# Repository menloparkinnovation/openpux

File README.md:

Openpux Internet Of Things (IOT) Framework
==========================================

Copyright (C) 2018 Menlo Park Innovation LLC

   menloparkinnovation.com
   menloparkinnovation@gmail.com

> Last update 03/07/2018

# Openpux Sub Projects

## openpux:

  Node.js based IoT server with in memory or Amazon SimpleDB data stores.

  > Development is frozen, as a serverless version openpux4 is in development.
  > Still useful as a local server for RaspberryPi, or small cloud IaaS VM's
    such as AWS LightSail.

## nodejs/dweet:

  Node.js utility providing both a command line embedded device configuration
          utility and IoT gateway on RaspberryPi, Mac, PC, or Linux.

## Arduino/Libraries:

  MenloFramework, a framework approach to creating embedded firmware for Arduino
  supporting AtMega328, AVR/Mega, and ARM32/SAM/Due. This has been validated
  against Arduino IDE 1.6.4 and test/regression scripts are in tests/mac.

  > The framework architecture also supports ports to RFDuino (ARM/BLE),
  > SparkCore, (Photon/Particle), and variants such as Galileo/Edison (x86/Linux).

  > Tested versions of these ports will be in future updates as re-validation
  > against the latest releases from these providers is in progress.

## Arduino/<project_name>:

  IoT projects using the MenloFramework and communicating with the openpux
  IoT server.

## Hardware:

  MenloPark Innovation LLC hardware projects for IoT scenarios.

  All projects use the Eagle design software, and generally fit within
  the free versions limits.

  Designs have been tested by generating boards from OshPark.

## FPGA Hardware:

  menlo_cnc - FPGA based CNC controller with embedded Linux.

  fpga/de10_nano_shell - Silicon Shell for Terasic DE110-Nano-SoC board.

  menlo_gigatron - FPGA implementation of the Gigatron (gigatron.io)

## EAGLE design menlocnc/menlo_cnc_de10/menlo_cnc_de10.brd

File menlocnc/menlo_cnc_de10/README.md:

MenloCNC Breakout board for Terasic DE10-Standard
=======================================================

Copyright (C) 2018 Menlo Park Innovation LLC

   menloparkinnovation.com
   menloparkinnovation@gmail.com

> Last update 06/11/2018

# Breakout board for Menlo CNC on DE10-Standard

  > Provides Arduino UNO pin outs for GRBL Shields

  > Provides Arduino MEGA pin outs for Mendel Shields

  > Provides general purpose I/O to FPGA pins

# Uses free version of Eagle Software

  > Most popular small board design software for open source projects

  > Used by Arduino, many others

# Boards Produced by OshPark

  > Popular service for low cost boards in about 2 weeks

  > 3 boards about $39

  > Can be produced by others from standard Eagle files

  > Or use Eagle to generate Gerber files

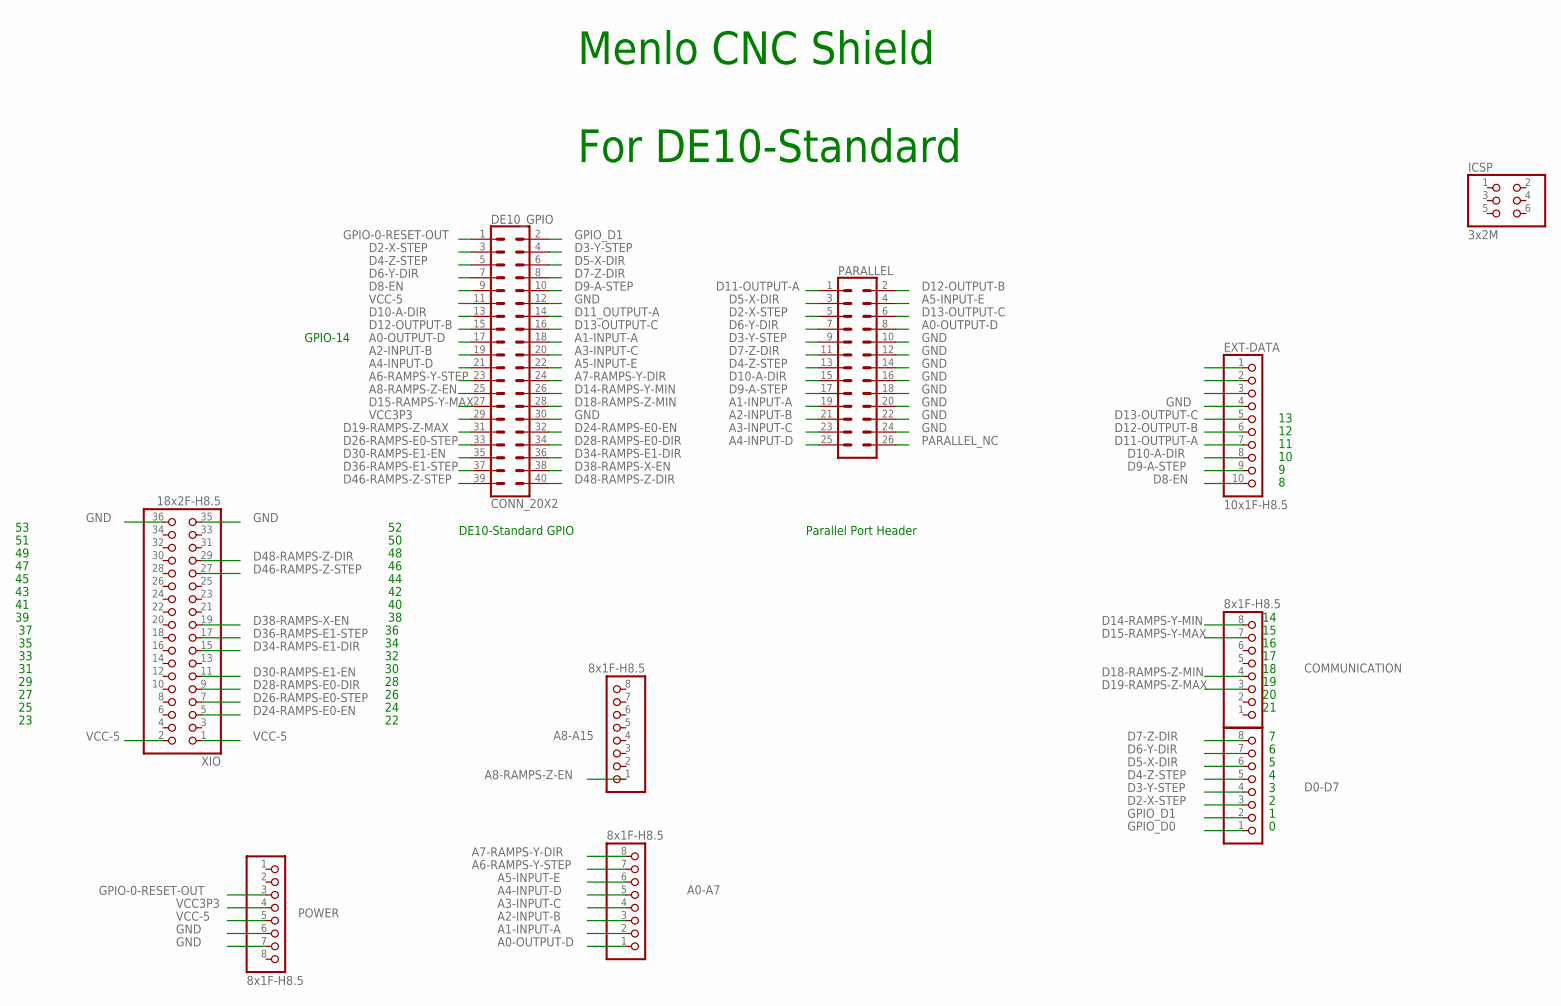
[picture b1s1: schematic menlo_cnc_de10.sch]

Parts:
A0-A7, A8-A15: 8x1F-H8.5; 1X08
COMMUNICATION: 8x1F-H8.5; 1X08
D0-D7: 8x1F-H8.5; 1X08
DE10_GPIO: CONN_20X2; 2X20
EXT-DATA: 10x1F-H8.5; 1X10
ICSP: 3x2M; 2X03
PARALLEL: CONN_13X22X13; 2X13
POWER: 8x1F-H8.5; 1X08
XIO: 18x2F-H8.5; 2X18

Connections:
A0-OUTPUT-D: A0-A7.1, DE10_GPIO.17, PARALLEL.8
A1-INPUT-A: A0-A7.2, DE10_GPIO.18, PARALLEL.19
A2-INPUT-B: A0-A7.3, DE10_GPIO.19, PARALLEL.21
A3-INPUT-C: A0-A7.4, DE10_GPIO.20, PARALLEL.23
A4-INPUT-D: A0-A7.5, DE10_GPIO.21, PARALLEL.25
A5-INPUT-E: A0-A7.6, DE10_GPIO.22, PARALLEL.4
A6-RAMPS-Y-STEP: A0-A7.7, DE10_GPIO.23
A7-RAMPS-Y-DIR: A0-A7.8, DE10_GPIO.24
A8-RAMPS-Z-EN: A8-A15.1, DE10_GPIO.25
D2-X-STEP: D0-D7.3, DE10_GPIO.3, PARALLEL.5
D3-Y-STEP: D0-D7.4, DE10_GPIO.4, PARALLEL.9
D4-Z-STEP: D0-D7.5, DE10_GPIO.5, PARALLEL.13
D5-X-DIR: D0-D7.6, DE10_GPIO.6, PARALLEL.3
D6-Y-DIR: D0-D7.7, DE10_GPIO.7, PARALLEL.7
D7-Z-DIR: D0-D7.8, DE10_GPIO.8, PARALLEL.11
D8-EN: DE10_GPIO.9, EXT-DATA.10
D9-A-STEP: DE10_GPIO.10, EXT-DATA.9, PARALLEL.17
D10-A-DIR: DE10_GPIO.13, EXT-DATA.8, PARALLEL.15
D11-OUTPUT-A: EXT-DATA.7, PARALLEL.1
D11_OUTPUT-A: DE10_GPIO.14
D12-OUTPUT-B: DE10_GPIO.15, EXT-DATA.6, PARALLEL.2
D13-OUTPUT-C: DE10_GPIO.16, EXT-DATA.5, PARALLEL.6
D14-RAMPS-Y-MIN: COMMUNICATION.8, DE10_GPIO.26
D15-RAMPS-Y-MAX: COMMUNICATION.7, DE10_GPIO.27
D18-RAMPS-Z-MIN: COMMUNICATION.4, DE10_GPIO.28
D19-RAMPS-Z-MAX: COMMUNICATION.3, DE10_GPIO.31
D24-RAMPS-E0-EN: DE10_GPIO.32, XIO.5
D26-RAMPS-E0-STEP: DE10_GPIO.33, XIO.7
D28-RAMPS-E0-DIR: DE10_GPIO.34, XIO.9
D30-RAMPS-E1-EN: DE10_GPIO.35, XIO.11
D34-RAMPS-E1-DIR: DE10_GPIO.36, XIO.15
D36-RAMPS-E1-STEP: DE10_GPIO.37, XIO.17
D38-RAMPS-X-EN: DE10_GPIO.38, XIO.19
D46-RAMPS-Z-STEP: DE10_GPIO.39, XIO.27
D48-RAMPS-Z-DIR: DE10_GPIO.40, XIO.29
GND: DE10_GPIO.12, DE10_GPIO.30, EXT-DATA.4, PARALLEL.10, PARALLEL.12, PARALLEL.14, PARALLEL.16, PARALLEL.18, PARALLEL.20, PARALLEL.22, PARALLEL.24, POWER.6, POWER.7, XIO.35, XIO.36
GPIO-0-RESET-OUT: DE10_GPIO.1, POWER.3
GPIO_D0: D0-D7.1
GPIO_D1: D0-D7.2, DE10_GPIO.2
PARALLEL_NC: PARALLEL.26
VCC3P3: DE10_GPIO.29, POWER.4
VCC-5: DE10_GPIO.11, POWER.5, XIO.1, XIO.2

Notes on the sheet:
Menlo CNC Shield For DE10-Standard
DE10-Standard GPIO
Parallel Port Header
GPIO-14

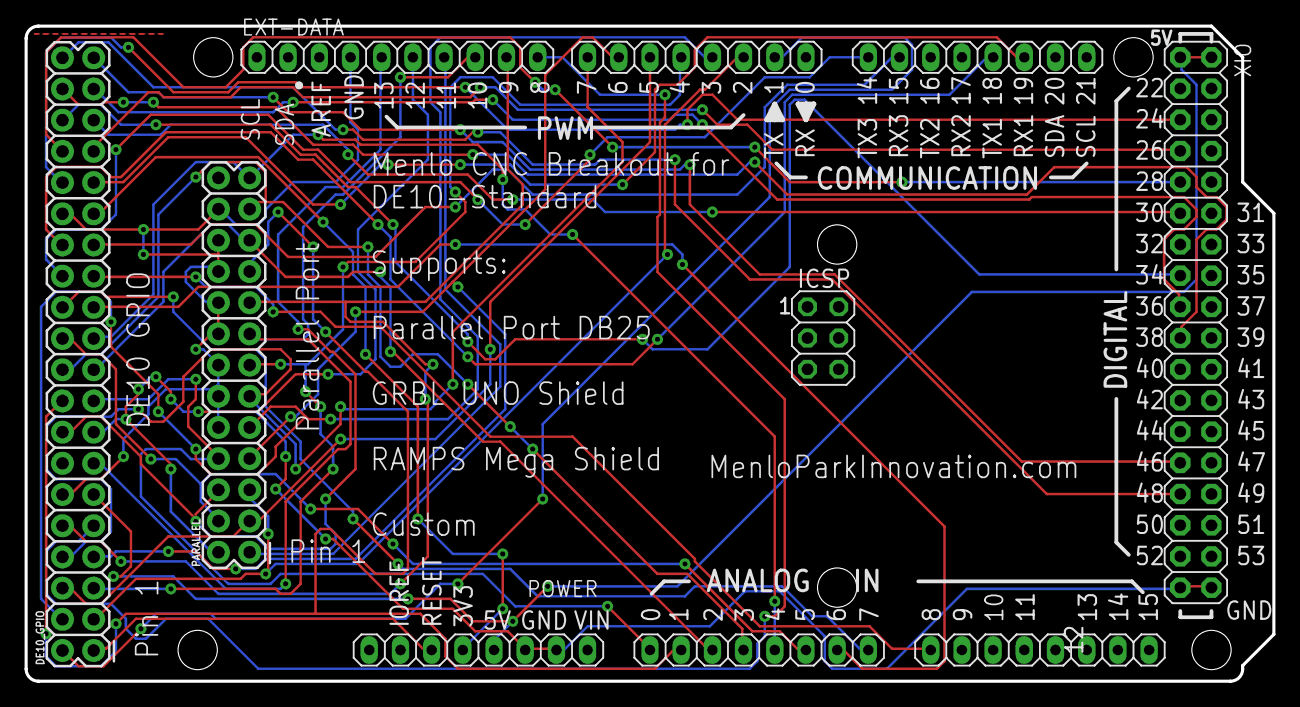
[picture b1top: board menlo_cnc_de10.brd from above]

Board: 2 copper layers, 101.6 x 53.3 mm, 10 parts (0 on the bottom side), 39 nets.

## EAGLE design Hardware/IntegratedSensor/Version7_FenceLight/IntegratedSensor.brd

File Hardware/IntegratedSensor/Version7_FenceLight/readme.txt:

06/30/2014

Updated from Version 6 to fix hole spacing.

06/15/2014

FenceLight holes and format/layout

Sent to oshpark.com 06/15/2014 4:00PM

MenloSensor with inline DIP AtMega 328p

This is really an experimentors board for hand soldering
through hole.

Provides the full gardenlight/plant monitor scenario, but
parts may be optionally populated, and the unused I/O's
and resistor slots used to configure other sensors.

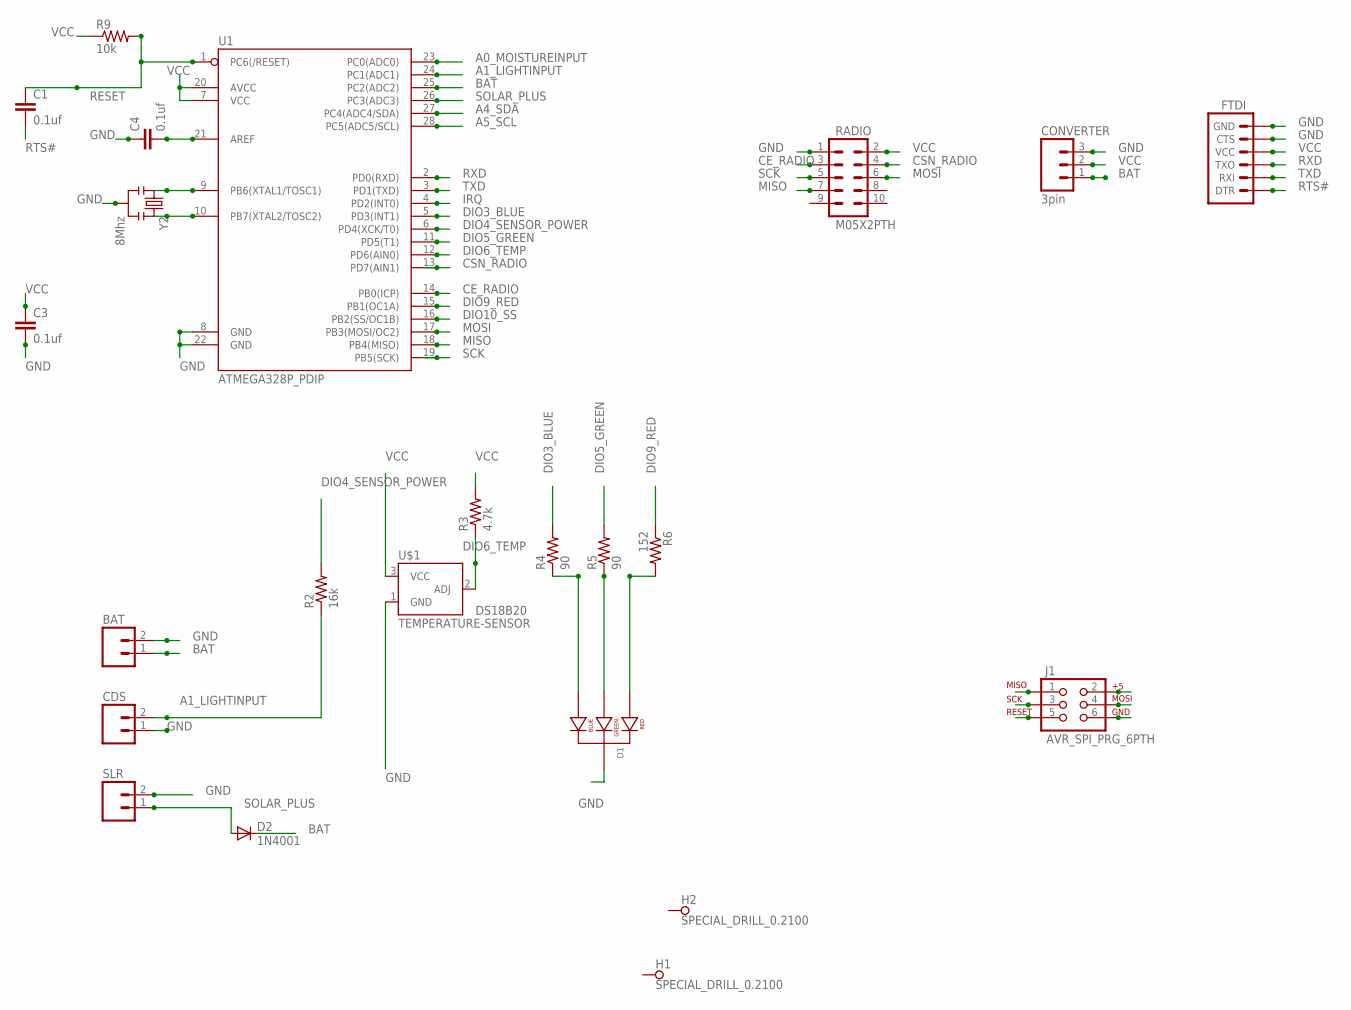
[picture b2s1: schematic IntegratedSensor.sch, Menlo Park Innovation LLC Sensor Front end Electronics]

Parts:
BAT: M02PTH; 1X02
C1, C3, C4: 0.1uf; CAP-PTH-SMALL
CDS: M02PTH; 1X02
CONVERTER: 3pin; 1X03
D1: LED-RGB-CC-THRUCLEAR; LED-RGB-THRU
D2: 1N4001; DIODE-1N4001
FTDI: ARDUINO_SERIAL_PROGRAMPTH; 1X06
H1, H2: SPECIAL_DRILL_0.2100; PAD_0.2100
J1: AVR_SPI_PRG_6PTH; 2X3
R2: 16k; 1/6W-RES
R3: 4.7k; 1/6W-RES
R4, R5: 90; 1/6W-RES
R6: 152; 1/6W-RES
R9: 10k; 1/6W-RES
RADIO: M05X2PTH; AVR_ICSP
SLR: M02PTH; 1X02
U1: ATMEGA328P_PDIP; DIL28-3
U$1: TEMPERATURE-SENSOR; TO-92; PARTNAME DS18B20
Y2: 8Mhz; RESONATOR-PTH

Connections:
A0_MOISTUREINPUT: U1.23 (PC0(ADC0))
A1_LIGHTINPUT: CDS.2, R2.1, U1.24 (PC1(ADC1))
A4_SDA: U1.27 (PC4(ADC4/SDA))
A5_SCL: U1.28 (PC5(ADC5/SCL))
BAT: BAT.1, CONVERTER.1, D2.C, U1.25 (PC2(ADC2))
CE_RADIO: RADIO.3, U1.14 (PB0(ICP))
CSN_RADIO: RADIO.4, U1.13 (PD7(AIN1))
DIO3_BLUE: R4.2, U1.5 (PD3(INT1))
DIO4_SENSOR_POWER: R2.2, U1.6 (PD4(XCK/T0))
DIO5_GREEN: R5.2, U1.11 (PD5(T1))
DIO6_TEMP: R3.1, U1.12 (PD6(AIN0)), U$1.2 (ADJ)
DIO9_RED: R6.1, U1.15 (PB1(OC1A))
DIO10_SS: U1.16 (PB2(SS/OC1B))
GND: BAT.2, C3.2, C4.1, CDS.1, CONVERTER.3, D1.2 (CATHODE), FTDI.5 (CTS), FTDI.6 (GND), J1.6, RADIO.1, SLR.2, U1.8 (GND), U1.22 (GND), U$1.1 (GND), Y2.2
IRQ: U1.4 (PD2(INT0))
MISO: J1.1, RADIO.7, U1.18 (PB4(MISO))
MOSI: J1.4, RADIO.6, U1.17 (PB3(MOSI/OC2))
unnamed: D1.4 (BLUE_CATHODE), R4.1
unnamed: D1.3 (GREEN_CATHODE), R5.1
unnamed: D1.1 (RED_CATHODE), R6.2
unnamed: U1.9 (PB6(XTAL1/TOSC1)), Y2.1
unnamed: U1.10 (PB7(XTAL2/TOSC2)), Y2.3
unnamed: C4.2, U1.21 (AREF)
RESET: C1.1, J1.5, R9.2, U1.1 (PC6(/RESET))
RTS#: C1.2, FTDI.1 (DTR)
RXD: FTDI.3 (TXO), U1.2 (PD0(RXD))
SCK: J1.3, RADIO.5, U1.19 (PB5(SCK))
SOLAR_PLUS: D2.A, SLR.1, U1.26 (PC3(ADC3))
TXD: FTDI.2 (RXI), U1.3 (PD1(TXD))
VCC: C3.1, CONVERTER.2, FTDI.4 (VCC), J1.2, R3.2, R9.1, RADIO.2, U1.7 (VCC), U1.20 (AVCC), U$1.3 (VCC)

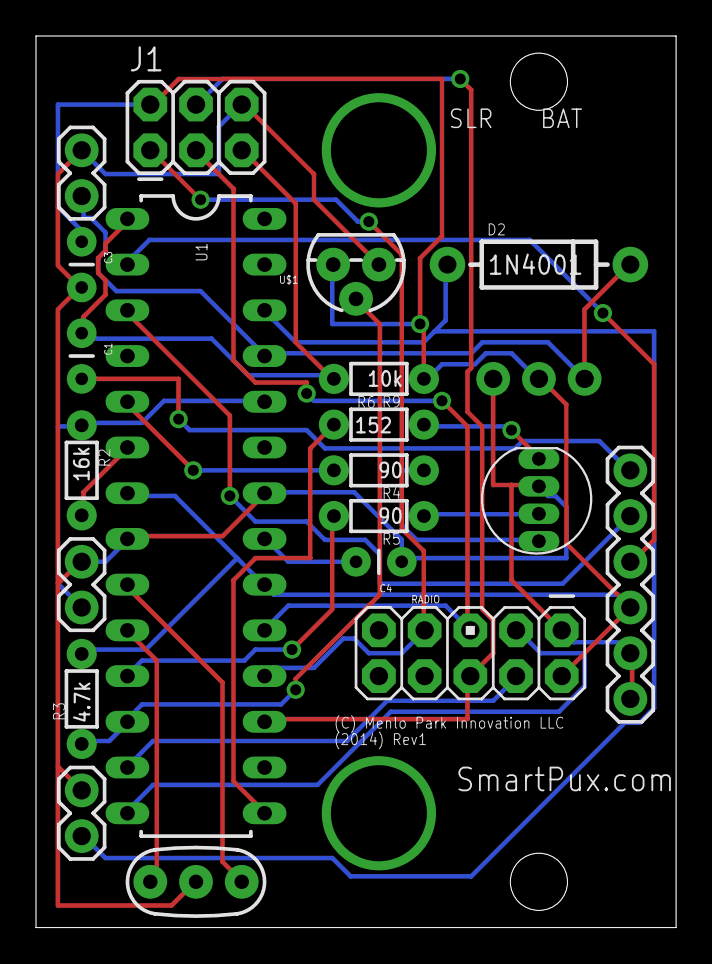
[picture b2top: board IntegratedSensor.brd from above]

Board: 2 copper layers, 35.6 x 49.5 mm, 25 parts (1 on the bottom side), 25 nets.

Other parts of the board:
U$2, U$3: DRILL_0.1250

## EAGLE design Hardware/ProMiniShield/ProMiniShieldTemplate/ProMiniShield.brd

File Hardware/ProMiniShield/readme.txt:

06/08/2015
ProMiniShieldLEDRotate is the latest design.

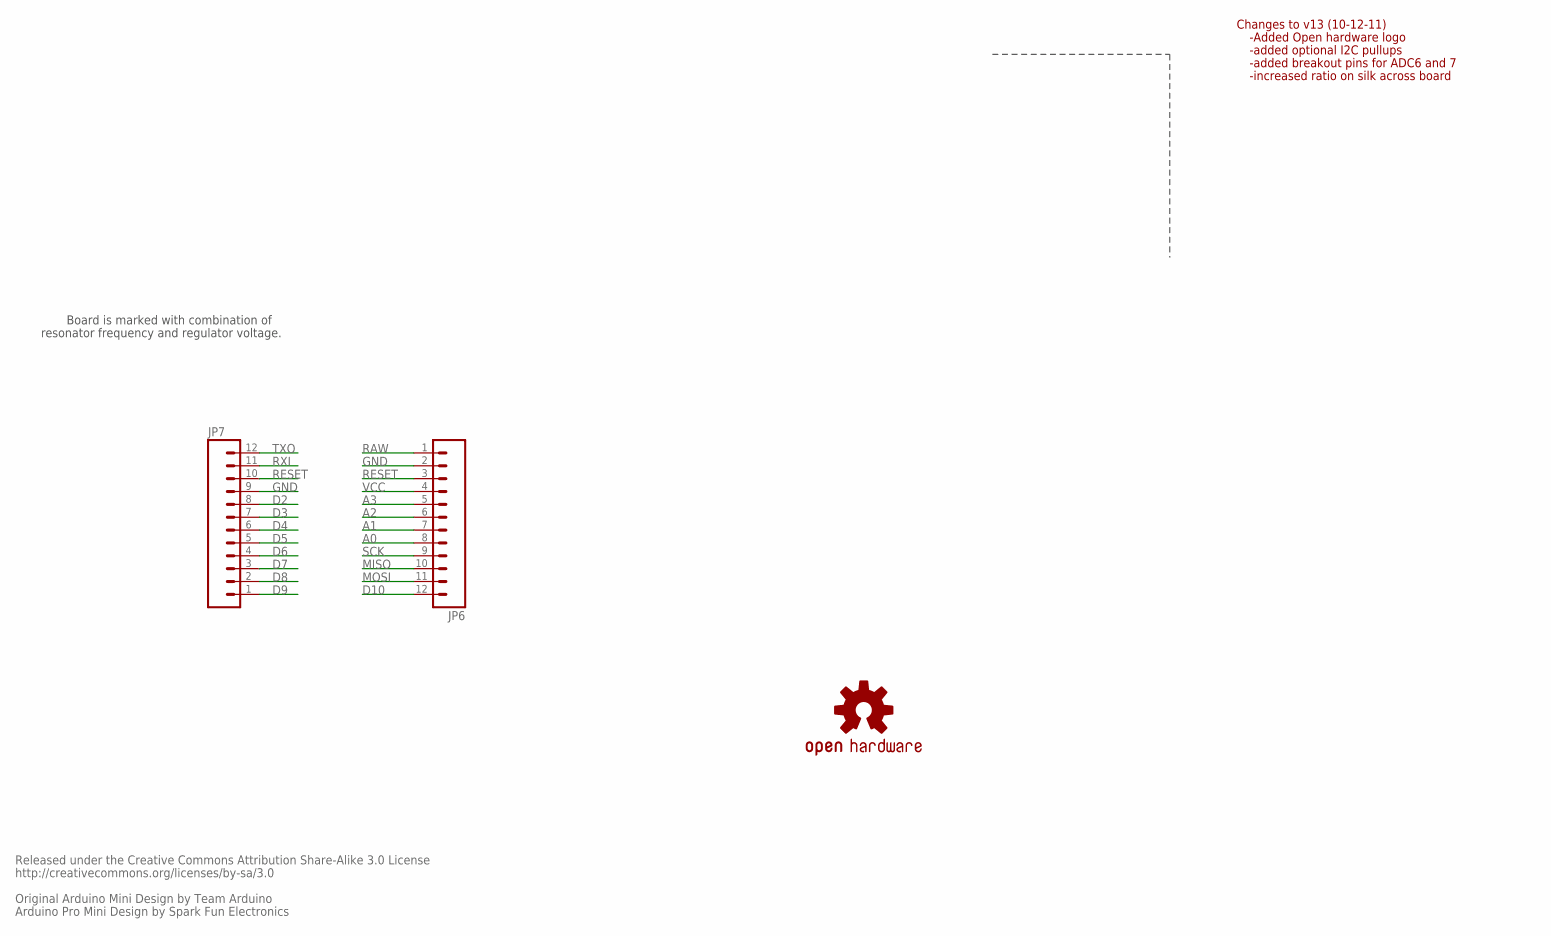
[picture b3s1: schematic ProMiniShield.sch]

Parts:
JP6, JP7: M12PTH; 1X12
U$3: OSHW-LOGOS; OSHW-LOGO-S

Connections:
A0: JP6.8
A1: JP6.7
A2: JP6.6
A3: JP6.5
D2: JP7.8
D3: JP7.7
D4: JP7.6
D5: JP7.5
D6: JP7.4
D7: JP7.3
D8: JP7.2
D9: JP7.1
D10: JP6.12
GND: JP6.2, JP7.9
MISO: JP6.10
MOSI: JP6.11
RAW: JP6.1
RESET: JP6.3, JP7.10
RXI: JP7.11
SCK: JP6.9
TXO: JP7.12
VCC: JP6.4

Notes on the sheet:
Released under the Creative Commons Attribution Share-Alike 3.0 License
http://creativecommons.org/licenses/by-sa/3.0
Original Arduino Mini Design by Team Arduino
Arduino Pro Mini Design by Spark Fun Electronics
Board is marked with combination of
resonator frequency and regulator voltage.
Changes to v13 (10-12-11)
-Added Open hardware logo
-added optional I2C pullups
-added breakout pins for ADC6 and 7
-increased ratio on silk across board

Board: 2 copper layers, 3 parts (3 on the bottom side), 2 nets, no tracks yet.

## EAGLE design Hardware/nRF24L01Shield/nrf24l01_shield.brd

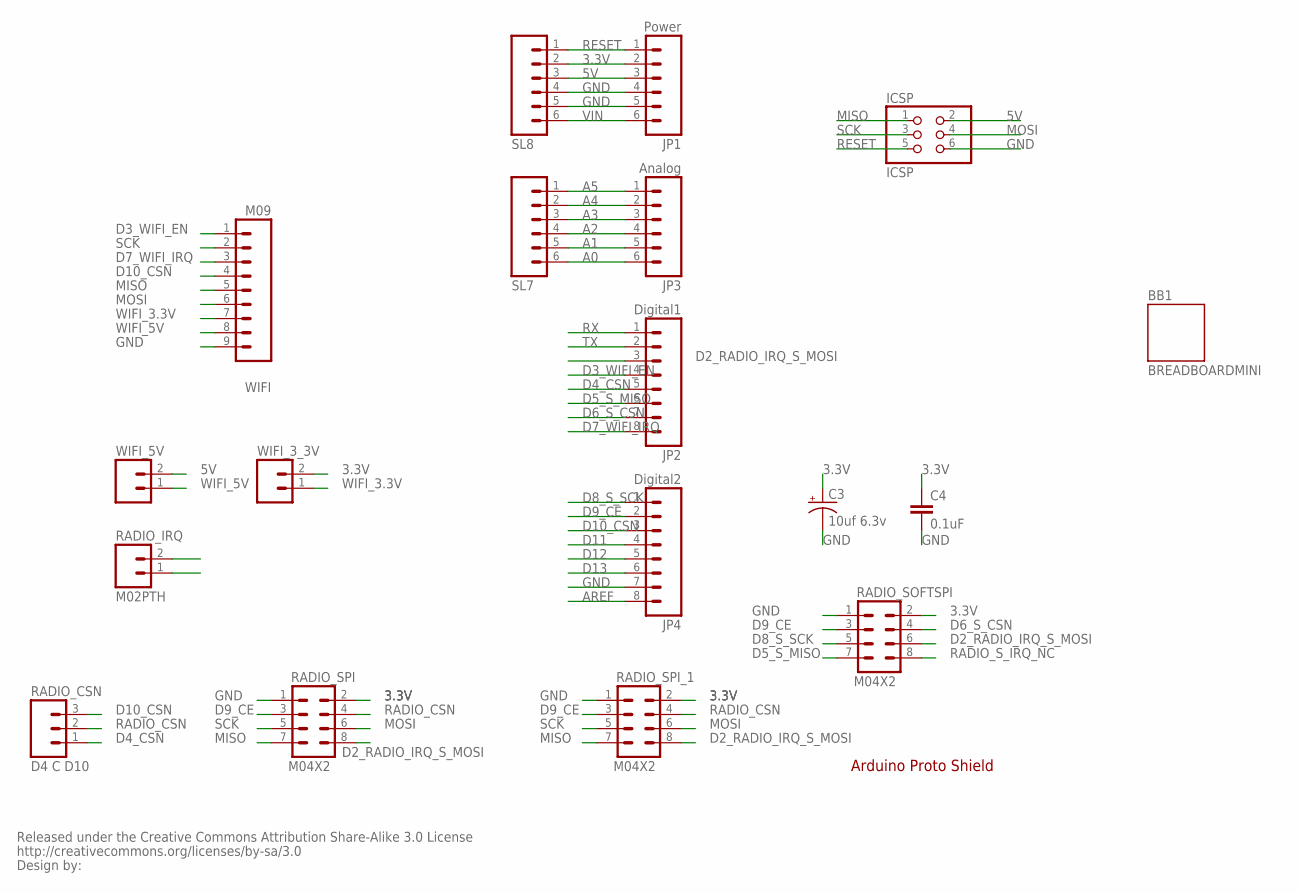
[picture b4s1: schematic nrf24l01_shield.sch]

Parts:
BB1: BREADBOARDMINI; BREADBOARD-MINI
C3: 10uf 6.3v; CPOL-RADIAL-10UF-25V
C4: 0.1uF; CAP-PTH-SMALL2
ICSP: ICSP; 2X03
JP1: Power; 1X06
JP2: Digital1; 1X08
JP3: Analog; 1X06
JP4: Digital2; 1X08
RADIO_CSN: D4 C D10; 1X03
RADIO_IRQ: M02PTH; 1X02
RADIO_SOFTSPI: M04X2; 2X4
RADIO_SPI: M04X2; 2X4
RADIO_SPI_1: M04X2; 2X4
SL7, SL8: M06SIP; 1X06
U$2: CREATIVE_COMMONS
WIFI: M09; 1X09
WIFI_3_3V, WIFI_5V: M02PTH; 1X02

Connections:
3.3V: C3.1 (+), C4.1, JP1.2, RADIO_SOFTSPI.2, RADIO_SPI.2, RADIO_SPI_1.2, SL8.2, WIFI_3_3V.2
5V: ICSP.2, JP1.3, SL8.3, WIFI_5V.2
A0: JP3.6, SL7.6
A1: JP3.5, SL7.5
A2: JP3.4, SL7.4
A3: JP3.3, SL7.3
A4: JP3.2, SL7.2
A5: JP3.1, SL7.1
AREF: JP4.8
D2_RADIO_IRQ_S_MOSI: JP2.3, RADIO_SOFTSPI.6, RADIO_SPI.8, RADIO_SPI_1.8
D3_WIFI_EN: JP2.4, WIFI.1
D4_CSN: JP2.5, RADIO_CSN.1
D5_S_MISO: JP2.6, RADIO_SOFTSPI.7
D6_S_CSN: JP2.7, RADIO_SOFTSPI.4
D7_WIFI_IRQ: JP2.8, WIFI.3
D8_S_SCK: JP4.1, RADIO_SOFTSPI.5
D9_CE: JP4.2, RADIO_SOFTSPI.3, RADIO_SPI.3, RADIO_SPI_1.3
D10_CSN: JP4.3, RADIO_CSN.3, WIFI.4
D11: JP4.4
D12: JP4.5
D13: JP4.6
GND: C3.2 (-), C4.2, ICSP.6, JP1.4, JP1.5, JP4.7, RADIO_SOFTSPI.1, RADIO_SPI.1, RADIO_SPI_1.1, SL8.4, SL8.5, WIFI.9
MISO: ICSP.1, RADIO_SPI.7, RADIO_SPI_1.7, WIFI.5
MOSI: ICSP.4, RADIO_SPI.6, RADIO_SPI_1.6, WIFI.6
RADIO_CSN: RADIO_CSN.2, RADIO_SPI.4, RADIO_SPI_1.4
RADIO_S_IRQ_NC: RADIO_SOFTSPI.8
RESET: ICSP.5, JP1.1, SL8.1
RX: JP2.1
SCK: ICSP.3, RADIO_SPI.5, RADIO_SPI_1.5, WIFI.2
TX: JP2.2
VIN: JP1.6, SL8.6
WIFI_3.3V: WIFI.7, WIFI_3_3V.1
WIFI_5V: WIFI.8, WIFI_5V.1

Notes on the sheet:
Arduino Proto Shield

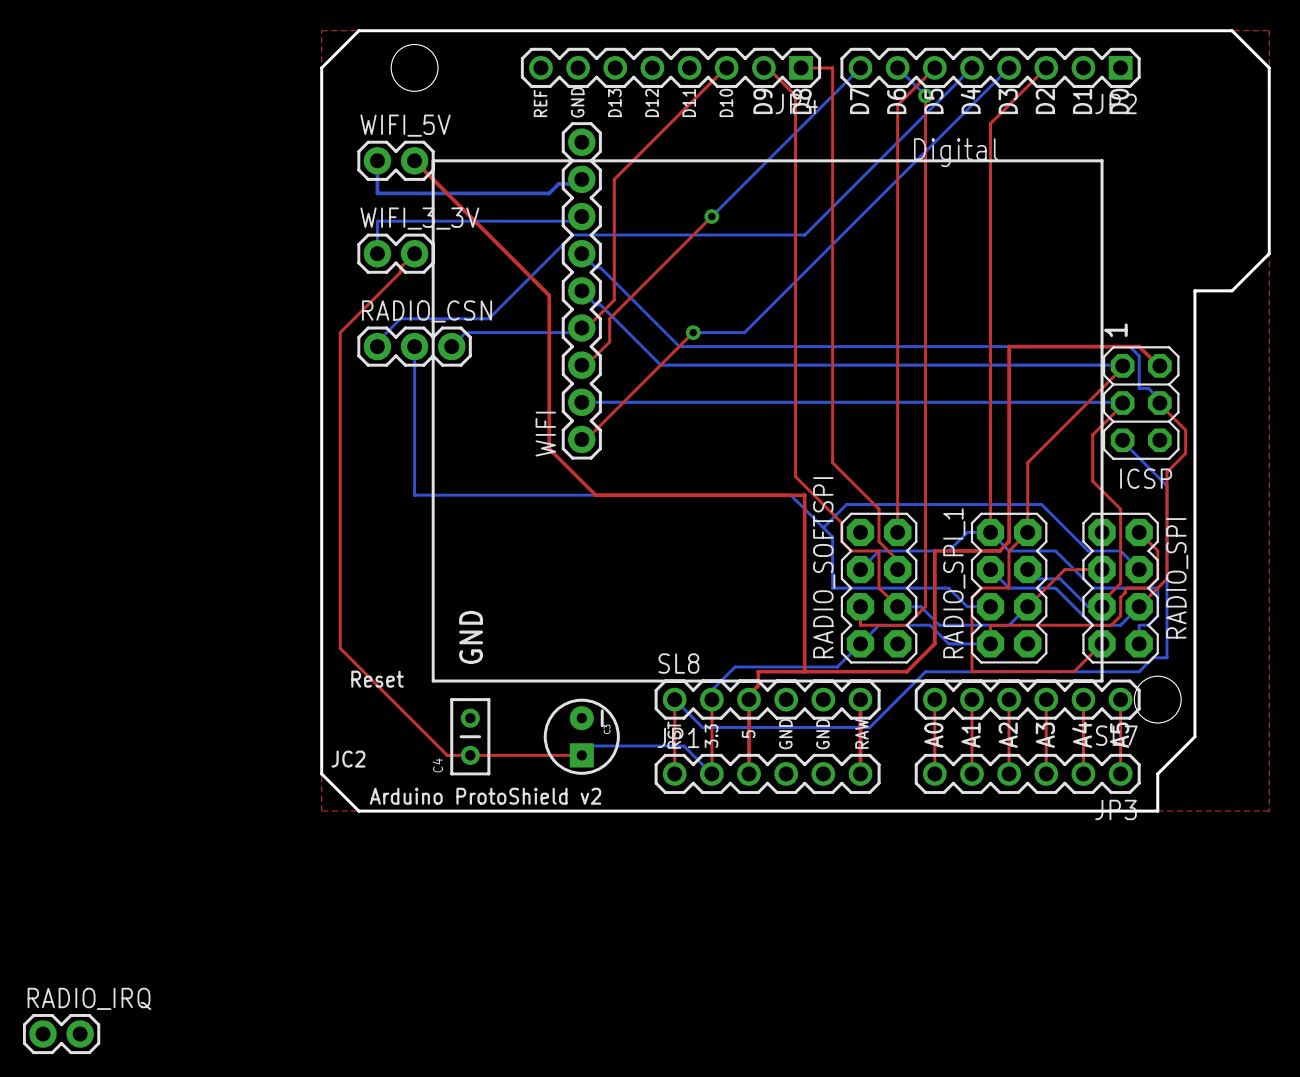
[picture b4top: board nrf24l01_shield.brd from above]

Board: 2 copper layers, 64.8 x 53.3 mm, 19 parts (0 on the bottom side), 26 nets.

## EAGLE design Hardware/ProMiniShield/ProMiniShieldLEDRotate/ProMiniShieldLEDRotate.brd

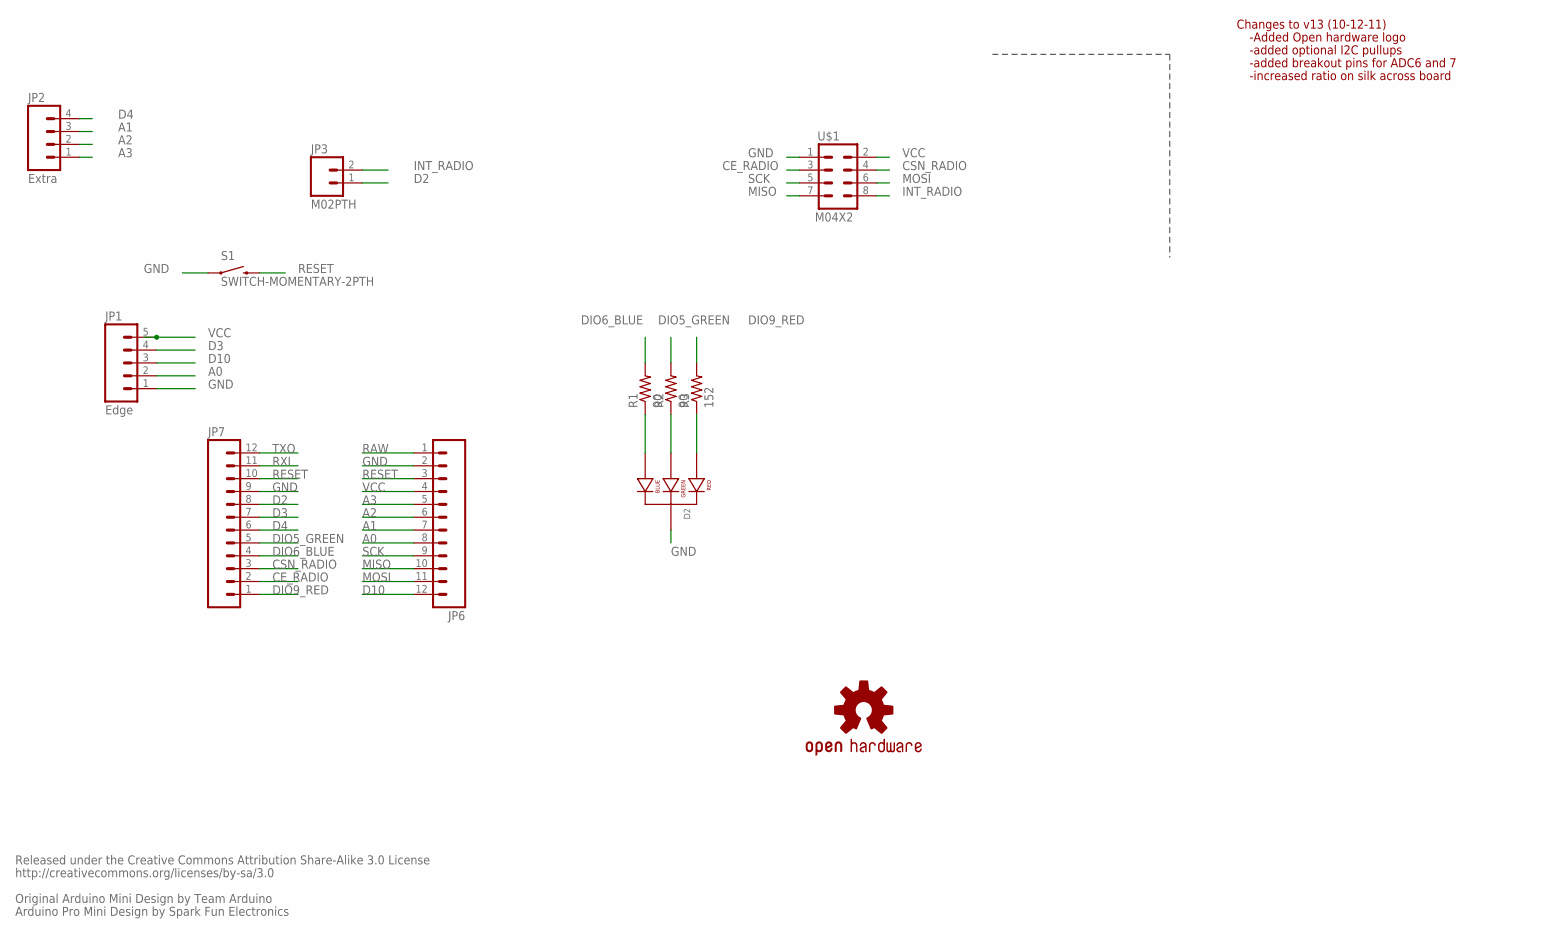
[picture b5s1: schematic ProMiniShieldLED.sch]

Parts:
D2: LED-RGB-CC-THRUCLEAR; LED-RGB-THRU
JP1: Edge; 1X05
JP2: Extra; 1X04
JP3: M02PTH; 1X02
JP6, JP7: M12PTH; 1X12
R1, R2: 90; 1/6W-RES
R3: 152; 1/6W-RES
S1: SWITCH-MOMENTARY-2PTH; TACTILE-PTH
U$1: M04X2; 2X4
U$3: OSHW-LOGOS; OSHW-LOGO-S

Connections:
A0: JP1.2, JP6.8
A1: JP2.3, JP6.7
A2: JP2.2, JP6.6
A3: JP2.1, JP6.5
CE_RADIO: JP7.2, U$1.3
CSN_RADIO: JP7.3, U$1.4
D2: JP3.1, JP7.8
D3: JP1.4, JP7.7
D4: JP2.4, JP7.6
D10: JP1.3, JP6.12
DIO5_GREEN: JP7.5, R2.2
DIO6_BLUE: JP7.4, R1.2
DIO9_RED: JP7.1, R3.2
GND: D2.2 (CATHODE), JP1.1, JP6.2, JP7.9, S1.1, U$1.1
INT_RADIO: JP3.2, U$1.8
MISO: JP6.10, U$1.7
MOSI: JP6.11, U$1.6
unnamed: D2.4 (BLUE_CATHODE), R1.1
unnamed: D2.3 (GREEN_CATHODE), R2.1
unnamed: D2.1 (RED_CATHODE), R3.1
RAW: JP6.1
RESET: JP6.3, JP7.10, S1.3 (2)
RXI: JP7.11
SCK: JP6.9, U$1.5
TXO: JP7.12
VCC: JP1.5, JP6.4, U$1.2

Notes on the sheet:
Released under the Creative Commons Attribution Share-Alike 3.0 License
http://creativecommons.org/licenses/by-sa/3.0
Original Arduino Mini Design by Team Arduino
Arduino Pro Mini Design by Spark Fun Electronics
Changes to v13 (10-12-11)
-Added Open hardware logo
-added optional I2C pullups
-added breakout pins for ADC6 and 7
-increased ratio on silk across board

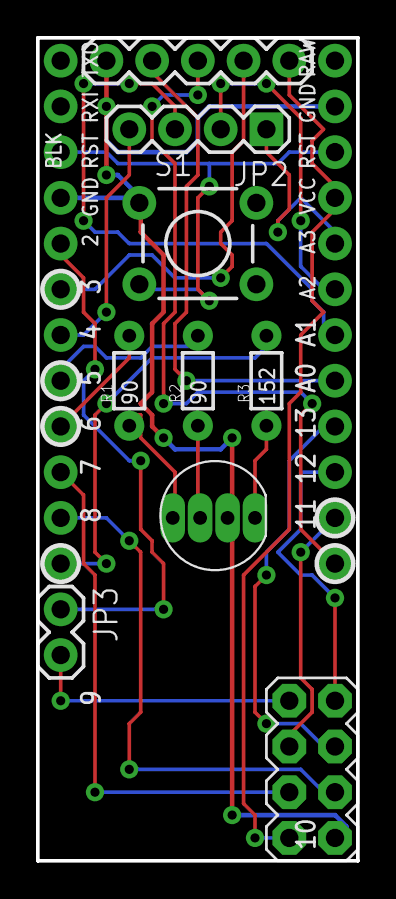
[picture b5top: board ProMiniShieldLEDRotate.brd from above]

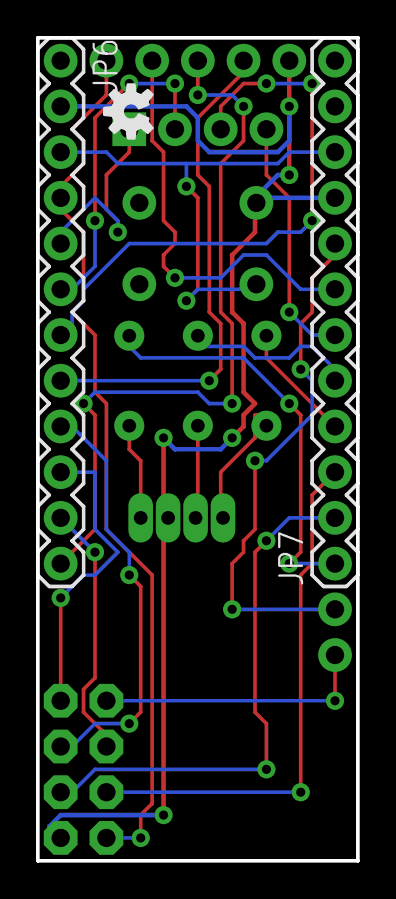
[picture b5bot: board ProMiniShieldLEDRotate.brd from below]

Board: 2 copper layers, 17.8 x 45.7 mm, 12 parts (3 on the bottom side), 23 nets.

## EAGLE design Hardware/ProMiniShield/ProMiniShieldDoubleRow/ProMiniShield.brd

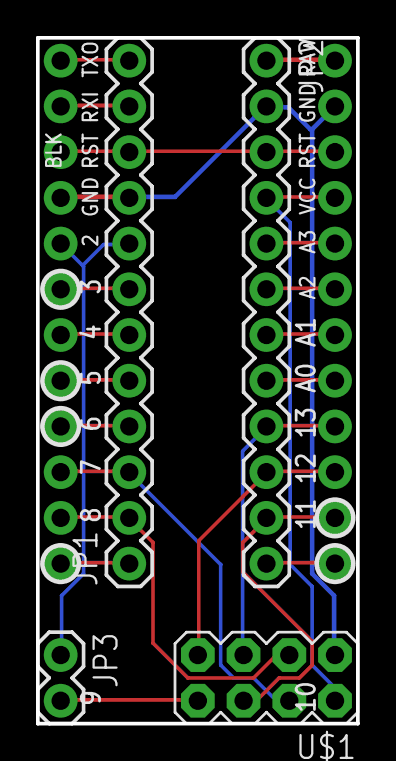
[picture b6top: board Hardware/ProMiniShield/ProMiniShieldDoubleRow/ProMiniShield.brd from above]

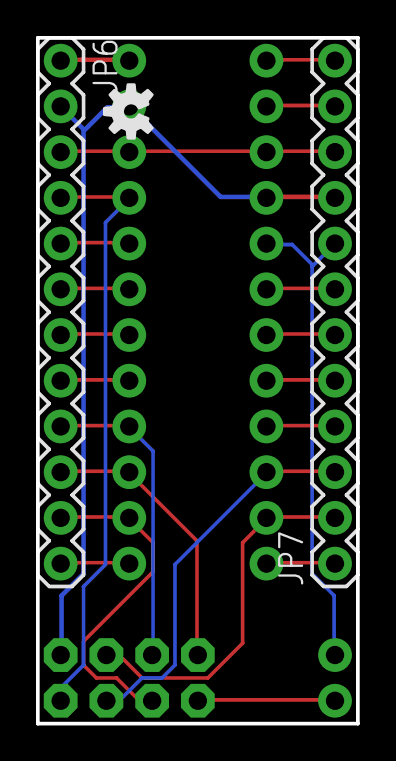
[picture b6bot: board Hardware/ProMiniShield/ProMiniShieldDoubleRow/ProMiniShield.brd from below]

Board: 2 copper layers, 17.8 x 38.1 mm, 7 parts (3 on the bottom side), 23 nets.

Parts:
JP1, JP2, JP6, JP7: 1X12
JP3: M02PTH; 1X02
U$1: M04X2; 2X4
U$3: OSHW-LOGOS; OSHW-LOGO-S

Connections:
A0: JP2.8, JP6.8
A1: JP2.7, JP6.7
A2: JP2.6, JP6.6
A3: JP2.5, JP6.5
CE_RADIO: JP1.2, JP7.2, U$1.3
CSN_RADIO: JP1.3, JP7.3, U$1.4
D2: JP1.8, JP3.1, JP7.8
D3: JP1.7, JP7.7
D4: JP1.6, JP7.6
D5: JP1.5, JP7.5
D6: JP1.4, JP7.4
D9: JP1.1, JP7.1
D10: JP2.12, JP6.12
GND: JP1.9, JP2.2, JP6.2, JP7.9, U$1.1
INT_RADIO: JP3.2, U$1.8
MISO: JP2.10, JP6.10, U$1.7
MOSI: JP2.11, JP6.11, U$1.6
RAW: JP2.1, JP6.1
RESET: JP1.10, JP2.3, JP6.3, JP7.10
RXI: JP1.11, JP7.11
SCK: JP2.9, JP6.9, U$1.5
TXO: JP1.12, JP7.12
VCC: JP2.4, JP6.4, U$1.2

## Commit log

2014-05-14 License File
2014-05-14 First Release
2014-05-15 Add Sensor Reading
2014-05-17 Connect Intel Galileo with Linux WiFi under Arduino environment
2014-05-17 Updated sensor processing
2014-05-18 Galileo sensor work
2014-05-20 Arduino test code
2014-05-21 plantmonitor
2014-05-21 Additional scenarios
2014-05-21 bug fixes
2014-05-22 Added automatic specialization
2014-05-22 fix typo
2014-05-26 DrinkCooler or Galileo
2014-05-27 DrinkCoolerSensorTest
2014-05-27 Specialization Support for core applications
2014-05-27 .gitignore
2014-05-27 remove old files, now uses specialization for common forms code
2014-05-27 removed old code
2014-07-14 DrinkCooler Documentation
2014-07-16 node utilities
2014-07-16 node.js utilities
2014-07-17 utility work
2014-07-21 remove stub code till working version is ready
2014-07-23 fix module stuff
2014-07-25 fix bugs
2014-07-27 async storage model
2014-07-27 async storage
2014-07-27 client.js work
2014-07-28 post support in menlohttprequest.js
2014-07-28 client utility
2014-07-29 fixes and updates
2014-07-29 client side utilities
2014-07-30 updated todo.txt
2014-08-04 test
2015-04-13 push test
2015-12-29 push to older version for new version upgrade
2016-01-04 Version 0.1.0 of Openpux, MenloFramework, Dweet, Hardware
2016-05-22 Add esp8266IotButton example
2016-05-22 configure for Azure hosting
2016-07-20 Summer 2016 Release
2016-11-27 add CHIP support
2016-11-27 Rebase to openpux/openpux
2018-03-05 March 2018 Libraries release for new projects
2018-03-08 March 2018 Release
2018-03-09 Cleanup comments
2018-03-11 Updated to npm nodeserial 6.x
2018-03-11 Update manual use of dweet through Arduino IDE serial monitor
2018-03-11 Cleanup MenloWatchDog.txt
2018-03-21 MenloCNC
2018-03-21 typo fixes
2018-06-11 initial snapshot of work in progress
2018-06-11 add breakout board
2018-06-13 assembler work
2018-06-18 remove deleted files
2018-06-18 assember and controller work
2018-06-18 verilog FPGA work
2018-06-23 support range and type postfix, perform range validation against machine
2018-06-23 add post fix range types, perform range validation against target machine
2018-06-25 working menlo_cnc_asm
2018-06-26 support INFO block
2018-06-29 Support full instruction decoder, DWELL, and PWM instructions
2018-06-29 app work
2018-07-02 menlo x74xxx series chips Verilog library
2018-09-06 Gigatron for DE10-Nano first release
2018-10-28 menlo silicon shell for de10_nano_soc
2018-10-28 update project list

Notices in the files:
parts and their libraries:
SparkFun-Sensors: Licensing: CC v3.0 Share-Alike You are welcome to use this library for commercial purposes.
SparkFun-Connectors: Licensing: Creative Commons ShareAlike 4.0 International - https://creativecommons.org/licenses/by-sa/4.0
